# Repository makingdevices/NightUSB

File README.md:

<!-- Improved compatibility of back to top link: See: https://github.com/othneildrew/Best-README-Template/pull/73 -->

<!--
*** Thanks for checking out the Best-README-Template. If you have a suggestion
*** that would make this better, please fork the repo and create a pull request
*** or simply open an issue with the tag "enhancement".
*** Don't forget to give the project a star!
*** Thanks again! Now go create something AMAZING! :D
-->

<!-- PROJECT SHIELDS -->
<!--
*** I'm using markdown "reference style" links for readability.
*** Reference links are enclosed in brackets [ ] instead of parentheses ( ).
*** See the bottom of this document for the declaration of the reference variables
*** for contributors-url, forks-url, etc. This is an optional, concise syntax you may use.
*** https://www.markdownguide.org/basic-syntax/#reference-style-links
-->
[![Instagram][ig-shield]][ig-url]
[![PCBWAY][sponsor-shield]][sponsor-url]
[![Stargazers][stars-shield]][stars-url]
[![Issues][issues-shield]][issues-url]
[![LinkedIn][linkedin-shield]][linkedin-url]

<!-- PROJECT LOGO -->
<br />
<div align="center">

<h3 align="center">Making Devices</h3>

  <p align="center">
    Open Source projects where we struggle with engineering, electronics, coding and who knows what else... Night USB is a very small USB dev board for the PIC18F14k50, so hopefully you may find it interesting ;)
  </p>
</div>

<!-- TABLE OF CONTENTS -->
<details>
  <summary>Table of Contents</summary>
  <ol>
    <li>
      <a href="#about-the-project">About The Project</a>
      <ul>
        <li><a href="#built-with">Built With</a></li>
      </ul>
    </li>
    <li>
      <a href="#Build-one">Build one</a>
      <ul>
      </ul>
    </li>
    <li><a href="#usage">Usage</a></li>
    <li><a href="#roadmap">Roadmap</a></li>
    <li><a href="#license">License</a></li>
    <li><a href="#contact">Contact</a></li>
    <li><a href="#Sponsor">Sponsor</a></li>
  </ol>
</details>

<!-- ABOUT THE PROJECT -->
## About The Project

[![Bytes Counter Shot][product-screenshot]](https://makingdevices.com/NightUSB)

The PIC18F14k50 is USB-2.0 fully compatible, so this small dev board aims to explore the USB communication: Simulating mouse, keyboard, make small scripts for BADUSB behaviour... And so much else can be done with this microcontroller! However, it does not count on isolation between the PIC and the USB, so it should be handled quite carefully. 

On the other hand, most of the IO pins of the PIC18F are available in the board, so even if you dont have any project with an USB, you can use the board as a normal dev board.

This project is finished, and the provided .hex file and software code is tested. The code simulates a small movement of the mouse every 15s, with a small blink of the LED. This will keep your PC alive for longer sesions of automated tests or anything else. (NOT FOR Remote work abuse!!)

<p align="right">(<a href="#readme-top">back to top</a>)</p>

### Built With

[![Microcontroller][PIC]][PIC-url]
[![MPLAB C][MPLAB-C]][MPLAB-C-url]
[![Kicad][kicad-shield]][kicad-url]
[![SPONSOR][sponsor-icon]][sponsor-url]

<p align="right">(<a href="#readme-top">back to top</a>)</p>

<!-- GETTING STARTED -->

## Build one
Documentation is updated.

1. Get the gerber files for the latest version: [V0.1](https://github.com/makingdevices/NightUSB/blob/main/Gerber/nightUSBv01.zip) 
2. Send them to a PCB manufacturer ([Our Sponsor is PCBWAY][sponsor-url])
3. You should solder all the components in the board. ([The schematic is available here v0.1][schematic-url])

<p align="right">(<a href="#readme-top">back to top</a>)</p>

<!-- USAGE EXAMPLES -->
## Usage

Instructions of use:

- The .hex files and software provided will emulate a mouse that will avoid your computer to go into sleep or standby.
- Dev Board. Only your imagination can tell you what to do with it :)

<p align="right">(<a href="#readme-top">back to top</a>)</p>

<!-- ROADMAP -->
## Roadmap

- [x] Finish the firmware for the PIC18F14K50
- [x] Assembly & First tests

See the [open issues](https://github.com/makingdevices/NightUSB/issues) for a full list of proposed features (and known issues).

State: Project <b>FINISHED</b> - 28/11/2023

<p align="right">(<a href="#readme-top">back to top</a>)</p>

<!-- LICENSE -->
## License

Distributed under three licenses:
- [Hardware](/License/HW_cern_ohl_s_v2.pdf)
- [Software](/License/SW_GPLv3.0.txt)
- [Documentation](/License/Documentation_CC-BY-SA-4.0.txt)

[![GPL v3 License][license-shield]][license-url] 
<p align="right">(<a href="#readme-top">back to top</a>)</p>

<!-- CONTACT -->
## Contact

Making Devices - [@MakingDevices](https://www.instagram.com/makingdevices/)

Project Link: [https://github.com/makingdevices/NightUSB](https://github.com/makingdevices/NightUSB/)

Other Links: [LinkTree](https://makingdevices.com/links/)

<p align="right">(<a href="#readme-top">back to top</a>)</p>

<!-- Sponsor -->
## Sponsor

[PCBWAY](https://www.pcbway.com/?from=makingdevices) is the most professional PCB manufacturer for prototyping and low-volume production to work with in the world. With more than a decade in the field, They are committed to meeting the needs of their customers from different industries in terms of quality, delivery, cost-effectiveness and any other demanding requests. As Sponsor of Making Devices, they will be in charge of all the PCBs for MDV, allowing both of us to grow together in a long term partnership. We hope you take them into account for your both personal and professional prototypes or products.

[![Sponsor Shot][sponsor-pcb-1]][sponsor-url]
[![Sponsor Shot][sponsor-pcb-2]][sponsor-url]

<!-- MARKDOWN LINKS & IMAGES -->
<!-- https://www.markdownguide.org/basic-syntax/#reference-style-links -->
[contributors-shield]: https://img.shields.io/github/contributors/makingdevices/NightUSB.svg?style=for-the-badge
[contributors-url]: https://github.com/makingdevices/NightUSB/graphs/contributors
[forks-shield]: https://img.shields.io/github/forks/makingdevices/NightUSB.svg?style=for-the-badge
[forks-url]: https://github.com/makingdevices/NightUSB/network/members
[stars-shield]: https://img.shields.io/github/stars/makingdevices/NightUSB.svg?style=for-the-badge
[stars-url]: https://github.com/makingdevices/NightUSB/stargazers
[issues-shield]: https://img.shields.io/github/issues/makingdevices/NightUSB.svg?style=for-the-badge
[issues-url]: https://github.com/makingdevices/NightUSB/issues
[license-shield]: /images/license.png
[license-url]: https://github.com/makingdevices/NightUSB/tree/main/License
[linkedin-shield]: https://img.shields.io/badge/-LinkedIn-black.svg?style=for-the-badge&logo=linkedin&colorB=555
[linkedin-url]: https://www.linkedin.com/company/making-devices/
[sponsor-shield]: https://img.shields.io/badge/SPONSOR-PCBWAY-black.svg?style=for-the-badge&colorB=1200
[sponsor-url]: https://www.pcbway.com/?from=makingdevices
[sponsor-screenshot]: /images/PCB_sponsor.png
[sponsor-pcb-1]: /images/usb_pcb1.jpg
[sponsor-pcb-2]: /images/usb_pcb2.jpg
[product-screenshot]: images/screenshot.jpg
[PIC]: https://img.shields.io/badge/PIC18F14K50-000000?style=for-the-badge
[PIC-url]: http://ww1.microchip.com/downloads/en/devicedoc/40001350f.pdf
[kicad-shield]: https://img.shields.io/badge/kicad-0b03fc?style=for-the-badge&logo=kicad&logoColor=white
[kicad-url]: https://www.kicad.org/
[YT-screenshot]: images/YT_assembly.PNG
[sponsor-icon]:  https://img.shields.io/badge/-PCBWAY-black.svg?style=for-the-badge&colorB=1200
[ig-shield]: https://img.shields.io/badge/instagram-a83297?style=for-the-badge&logo=instagram&logoColor=white
[ig-url]: https://www.instagram.com/makingdevices/
[MPLAB-C]: https://img.shields.io/badge/MPLAB%20C18-DD0031?style=for-the-badge&logo=C&logoColor=white
[MPLAB-C-url]: https://www.microchip.com/en-us/development-tool/SW006011
[Svelte.dev]: https://img.shields.io/badge/Svelte-4A4A55?style=for-the-badge&logo=svelte&logoColor=FF3E00
[Svelte-url]: https://svelte.dev/
[Laravel.com]: https://img.shields.io/badge/Laravel-FF2D20?style=for-the-badge&logo=laravel&logoColor=white
[Laravel-url]: https://laravel.com
[Bootstrap.com]: https://img.shields.io/badge/Bootstrap-563D7C?style=for-the-badge&logo=bootstrap&logoColor=white
[Bootstrap-url]: https://getbootstrap.com
[JQuery.com]: https://img.shields.io/badge/jQuery-0769AD?style=for-the-badge&logo=jquery&logoColor=white
[JQuery-url]: https://jquery.com 
[schematic-url]: /Output_PDF/Schematic_V0_1.pdf

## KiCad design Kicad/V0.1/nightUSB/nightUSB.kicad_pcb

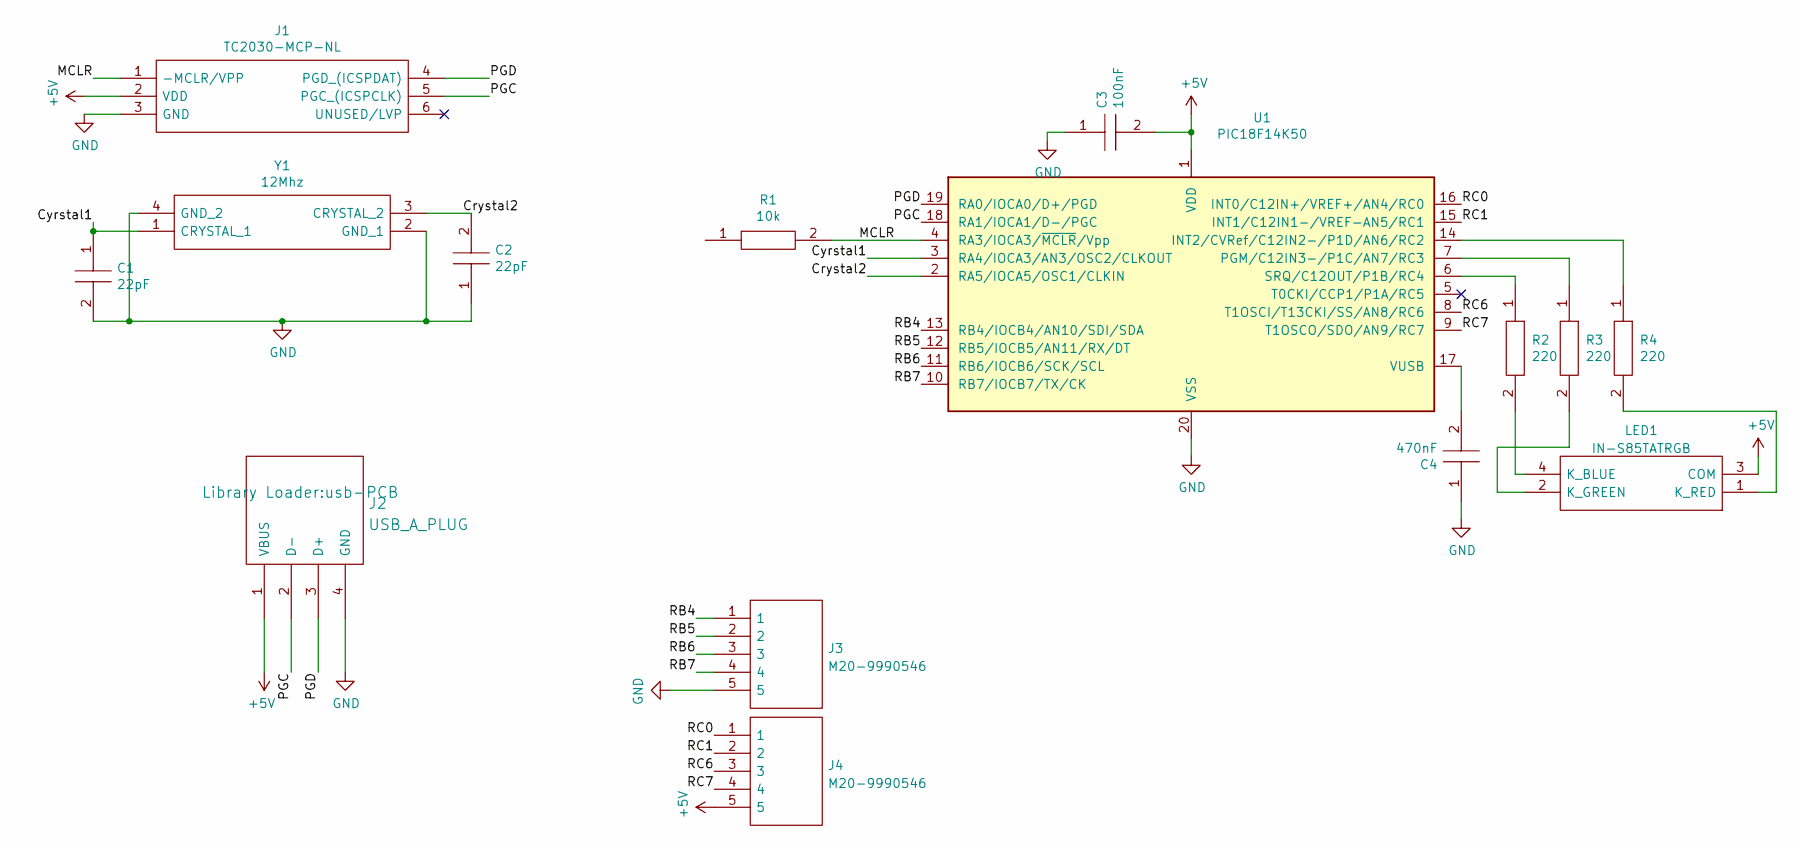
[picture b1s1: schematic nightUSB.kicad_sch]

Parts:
C1, C2: 22pF; CAPC2012X140N; Manufacturer_Part_Number C0805C475M8RACTU
C3: 100nF; CAPC2012X140N; Manufacturer_Part_Number C0805C475M8RACTU
C4: 470nF; CAPC2012X140N; Manufacturer_Part_Number C0805C475M8RACTU
J1: TC2030-MCP-NL; Manufacturer_Part_Number TC2030-MCP-NL
J2: USB_A_PLUG; usb-PCB
J3, J4: M20-9990546; HDRV5W64P0X254_1X5_1270X254X610P; Mouser Part Number 855-M20-9990546
LED1: IN-S85TATRGB; INS85DATRG; Mouser Part Number 743-IN-S85TATRGB
R1: 10k; RESC2012X75N; Manufacturer_Part_Number ERJP6WF1303V
R2, R3, R4: 220; RESC2012X75N; Manufacturer_Part_Number ERJP6WF1303V
U1: PIC18F14K50; SSOP-20_5.3x7.2mm_P0.65mm
Y1: 12Mhz; CX2520DB12000D0GPSC1; Manufacturer_Part_Number CX2520DB12000D0GPSC1

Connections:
+5V: C3.2, J1.2 (VDD), J2.1 (VBUS), J4.5, LED1.3 (COM), U1.1 (VDD)
/Crystal2: C2.2, U1.2 (RA5/IOCA5/OSC1/CLKIN), Y1.3 (CRYSTAL_2)
/Cyrstal1: C1.1, U1.3 (RA4/IOCA3/AN3/OSC2/CLKOUT), Y1.1 (CRYSTAL_1)
/MCLR: J1.1 (-MCLR/VPP), R1.2, U1.4 (RA3/IOCA3/~MCLR/Vpp)
/PGC: J1.5 (PGC_(ICSPCLK)), J2.2 (D-), U1.18 (RA1/IOCA1/D-/PGC)
/PGD: J1.4 (PGD_(ICSPDAT)), J2.3 (D+), U1.19 (RA0/IOCA0/D+/PGD)
/RB4: J3.1, U1.13 (RB4/IOCB4/AN10/SDI/SDA)
/RB5: J3.2, U1.12 (RB5/IOCB5/AN11/RX/DT)
/RB6: J3.3, U1.11 (RB6/IOCB6/SCK/SCL)
/RB7: J3.4, U1.10 (RB7/IOCB7/TX/CK)
/RC0: J4.1, U1.16 (INT0/C12IN+/VREF+/AN4/RC0)
/RC1: J4.2, U1.15 (INT1/C12IN1-/VREF-AN5/RC1)
/RC6: J4.3, U1.8 (T1OSCI/T13CKI/SS/AN8/RC6)
/RC7: J4.4, U1.9 (T1OSCO/SDO/AN9/RC7)
GND: C1.2, C2.1, C3.1, C4.1, J1.3 (GND), J2.4 (GND), J3.5, U1.20 (VSS), Y1.2 (GND_1), Y1.4 (GND_2)
unnamed: C4.2, U1.17 (VUSB)
unnamed: LED1.1 (K_RED), R4.2
unnamed: LED1.4 (K_BLUE), R2.2
unnamed: LED1.2 (K_GREEN), R3.2
unnamed: R2.1, U1.6 (SRQ/C12OUT/P1B/RC4)
unnamed: R3.1, U1.7 (PGM/C12IN3-/P1C/AN7/RC3)
unnamed: R4.1, U1.14 (INT2/CVRef/C12IN2-/P1D/AN6/RC2)

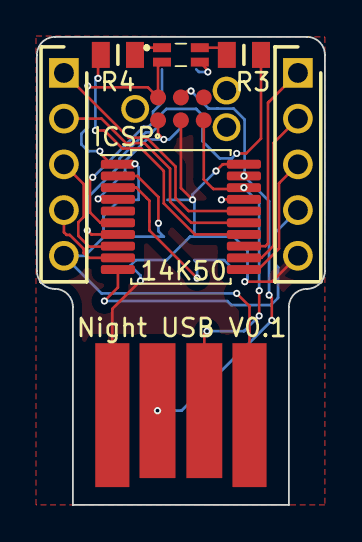
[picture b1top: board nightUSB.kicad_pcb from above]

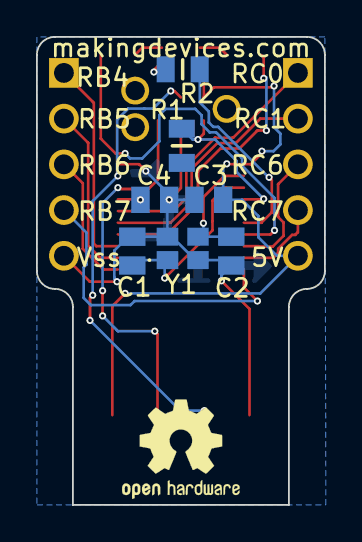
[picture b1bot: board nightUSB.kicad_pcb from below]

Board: 2 copper layers, 16.0 x 26.0 mm, 15 parts (7 on the bottom side), 22 nets.

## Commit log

2023-01-08 no message
2023-11-23 Firmware Release
2023-11-28 Update documentation
